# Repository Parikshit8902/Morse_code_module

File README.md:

# Morse_code_module
A morse code generator module which accepts input in morse code language and displays corresponding English character on the screen.
The files contain PCB design as well as Schematic design.
The components used are as follows:

1. ATMEGA328P-PU MCU
2. 16x2 LCD Display for displaying output
3. Buzzer
4. LED
5. Tactile Switch for accepting input
6. P-Mosfet for power-gating
7. LM2596 charging module
8. Batteries

The buzzer beeps based on the type of input provided by the user. The corresponding character is displayed on the screen.

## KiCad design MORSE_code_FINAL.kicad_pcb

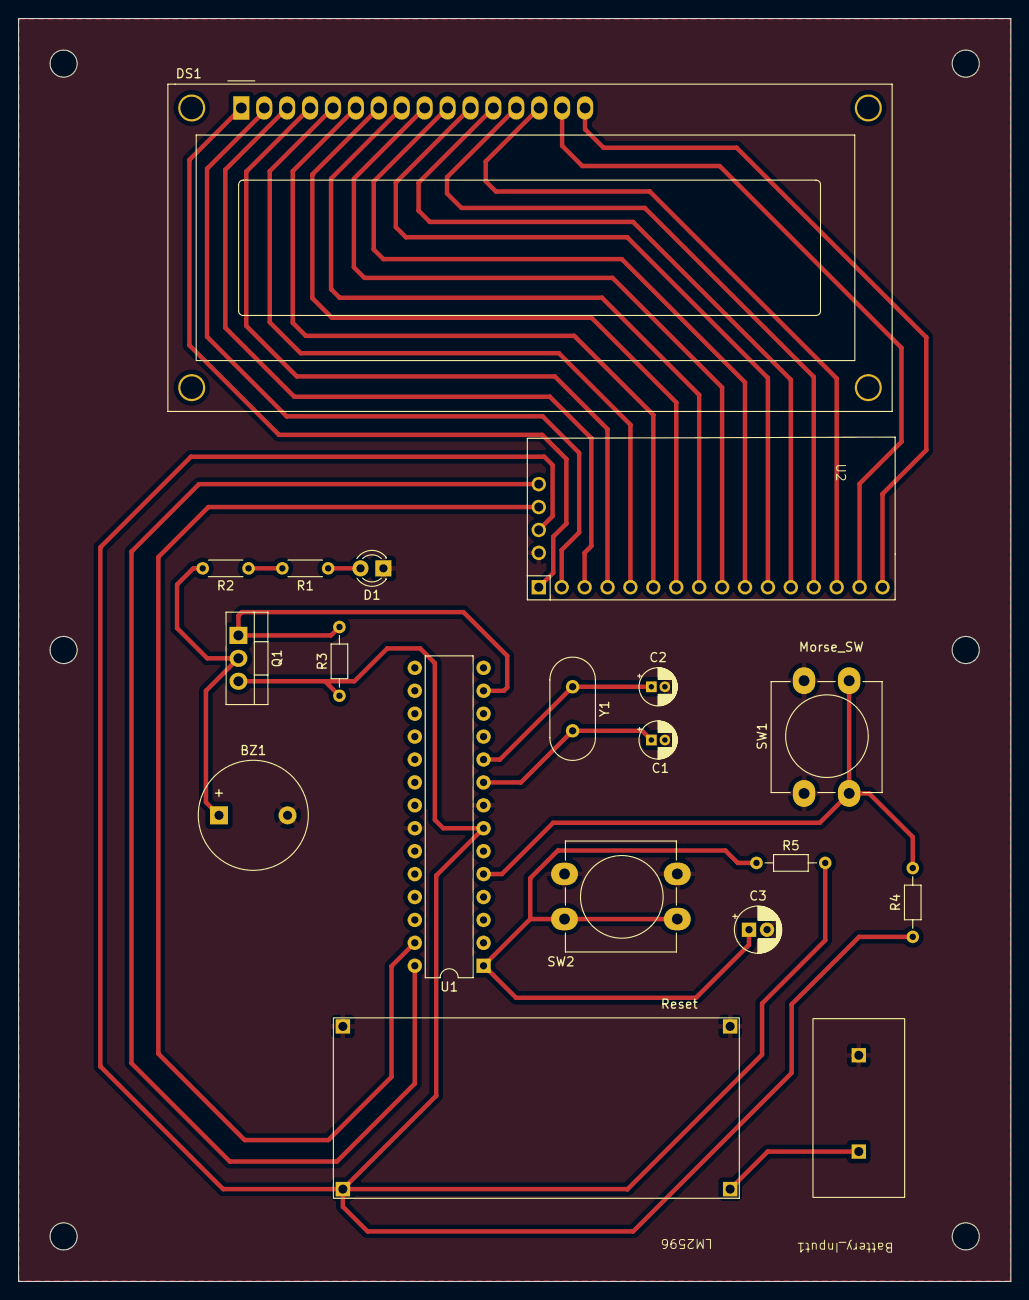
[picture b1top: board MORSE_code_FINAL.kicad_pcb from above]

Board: 2 copper layers, 110.0 x 140.0 mm, 19 parts (0 on the bottom side), 29 nets.

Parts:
BZ1: Buzzer; Buzzer_12x9.5RM7.6
Battery_Input1: Battery_Input
C1, C2: 22pF; CP_Radial_D4.0mm_P1.50mm
C3: 100nF; CP_Radial_D5.0mm_P2.00mm
D1: LED; LED_D3.0mm
DS1: WC1602A
LM2596: LM2596
Q1: IRF9540N; TO-220-3_Vertical
R1, R2: 220; R_Axial_DIN0204_L3.6mm_D1.6mm_P5.08mm_Horizontal
R3, R4, R5: 10K; R_Axial_DIN0204_L3.6mm_D1.6mm_P7.62mm_Horizontal
SW1, SW2: SW_MEC_5E; SW_PUSH-12mm_Wuerth-430476085716
U1: ATmega328P-P; DIP-28_W7.62mm
U2: I2C_16x2
Y1: Crystal; Crystal_HC49-4H_Vertical

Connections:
12V: Battery_Input1.12V, LM2596.1
GND: BZ1.2 (+), Battery_Input1.GND, C1.2, C2.2, C3.2, D1.1 (K), LM2596.3, LM2596.4, SW1.1, SW2.1, U1.8 (GND), U1.22 (GND), U2.GND
unnamed: BZ1.1 (-), Q1.2 (D), R2.2
unnamed: D1.2 (A), R1.1
unnamed: DS1.7 (D0), U2.7
unnamed: DS1.8 (D1), U2.8
unnamed: DS1.9 (D2), U2.9
unnamed: DS1.10 (D3), U2.10
unnamed: DS1.11 (D4), U2.11
unnamed: DS1.12 (D5), U2.12
unnamed: DS1.13 (D6), U2.13
unnamed: DS1.14 (D7), U2.14
unnamed: DS1.6 (E), U2.6
unnamed: DS1.15 (LED(+)), U2.15
unnamed: DS1.16 (LED(-)), U2.16
unnamed: DS1.4 (RS), U2.4
unnamed: DS1.5 (R/W), U2.5
unnamed: DS1.2 (VDD), U2.2
unnamed: DS1.3 (VO), U2.3
unnamed: DS1.1 (VSS), U2.1
unnamed: LM2596.2, Q1.3 (S), R3.1, R4.1, R5.2, U1.7 (VCC), U2.VCC
unnamed: Q1.1 (G), R3.2, U1.13 (PD7)
unnamed: R1.2, R2.1
unnamed: U1.27 (PC4), U2.SDA
unnamed: U1.28 (PC5), U2.SCL
unnamed: R4.2, SW1.2, U1.5 (PD3)
unnamed: C1.1, U1.9 (XTAL1/PB6), Y1.2
unnamed: C2.1, U1.10 (XTAL2/PB7), Y1.1
unnamed: C3.1, R5.1, SW2.2, U1.1 (~RESET/PC6)
